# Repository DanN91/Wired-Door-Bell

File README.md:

# Wired-Door-Bell

Hear your favourite song played whenever someone rings your doorbell.

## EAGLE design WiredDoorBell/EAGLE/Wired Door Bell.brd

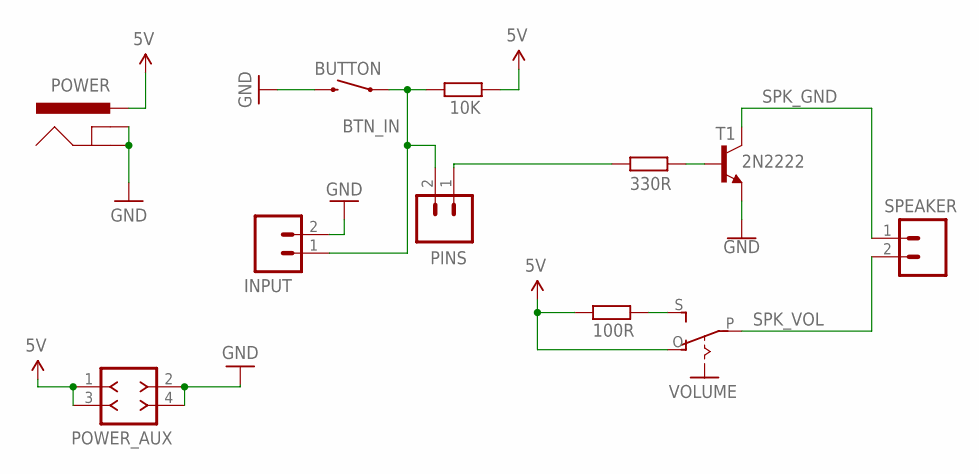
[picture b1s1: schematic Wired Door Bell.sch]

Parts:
10K: 10k; 0309V
100R: 100; 0309V
330R: 330; 0309V
BUTTON: MOMENTARY-SWITCH-SPST-PTH-6.0MM; TACTILE_SWITCH_PTH_6.0MM
INPUT: CONN_02; 1X02
PINS: CONN_02; 1X02
POWER: POWER_JACK; POWER_JACK_PTH
POWER_AUX: F-2X02-DIL-100; DIL-100-2X02
SPEAKER: CONN_02; 1X02
T1: 2N2222; TO92-EBC-OVAL
VOLUME: EG1218S; EG1218

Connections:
5V: 10K.2, 100R.1, POWER.PWR, POWER_AUX.1, POWER_AUX.3, VOLUME.O
BTN_IN: 10K.1, BUTTON.1, INPUT.1, PINS.2
GND: BUTTON.3 (2), INPUT.2, POWER.GND, POWER.GNDBREAK, POWER_AUX.2, POWER_AUX.4, T1.E
MIN: 100R.2, VOLUME.S
SPK_GND: SPEAKER.1, T1.C
SPK_PWM: 330R.1, PINS.1
SPK_SIG: 330R.2, T1.B
SPK_VOL: SPEAKER.2, VOLUME.P

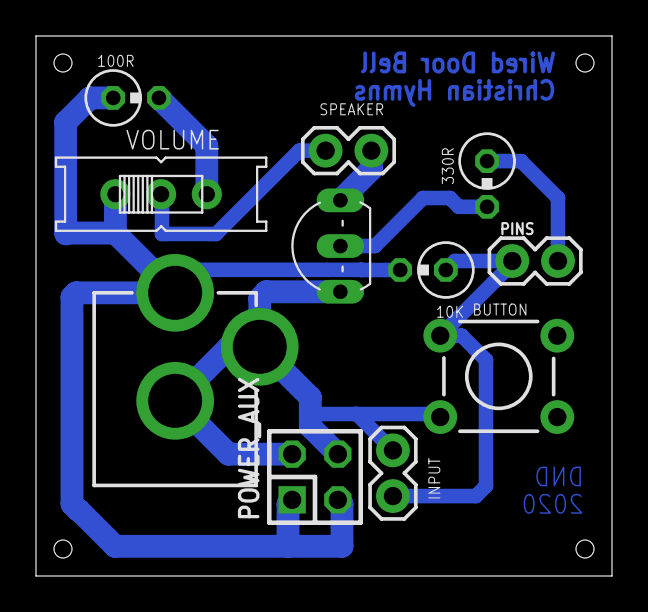
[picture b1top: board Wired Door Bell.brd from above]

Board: 2 copper layers, 32.0 x 30.0 mm, 11 parts (0 on the bottom side), 8 nets.

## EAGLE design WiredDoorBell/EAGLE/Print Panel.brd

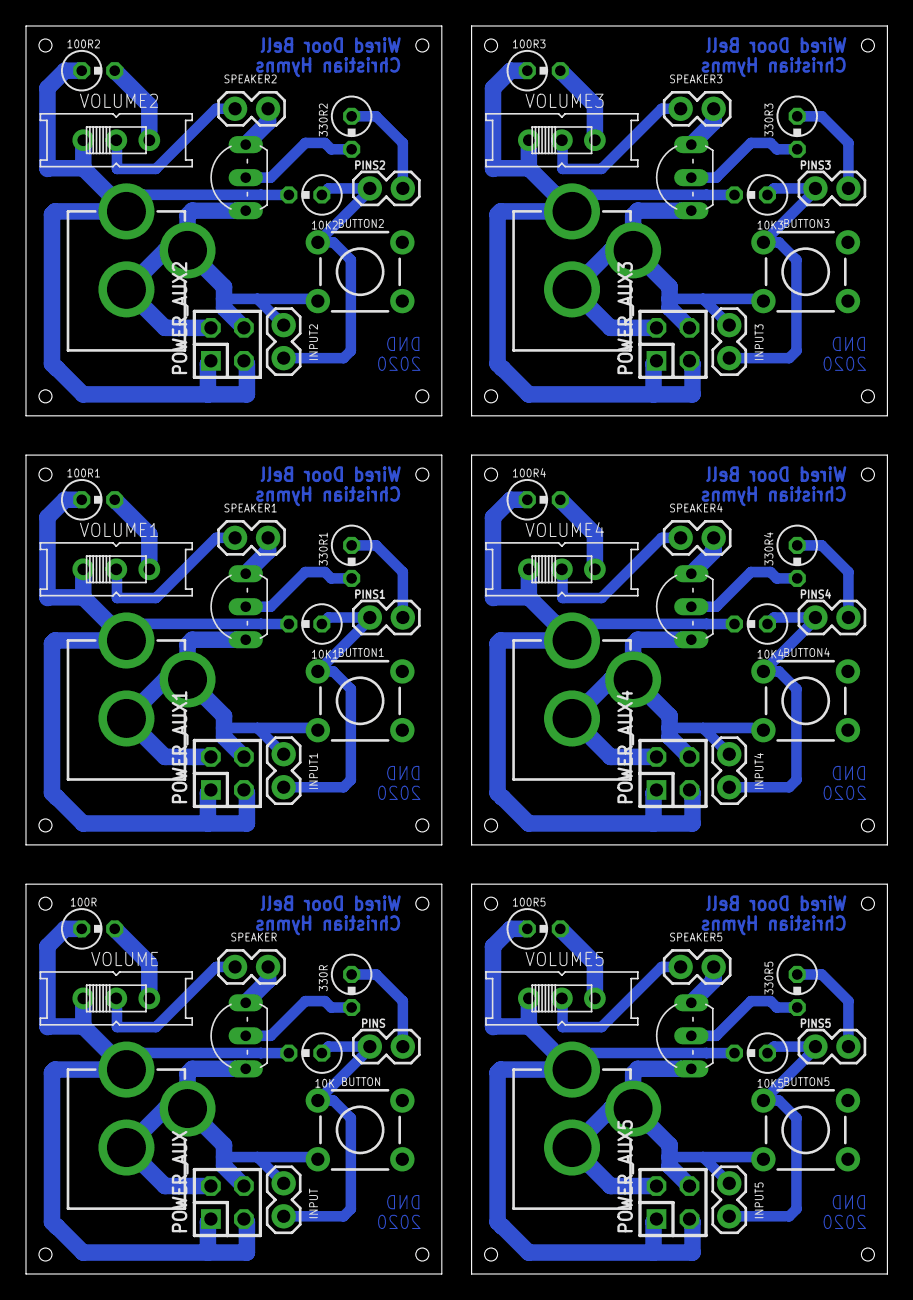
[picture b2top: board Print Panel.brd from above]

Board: 2 copper layers, 66.3 x 96.0 mm, 66 parts (0 on the bottom side), 48 nets.

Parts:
10K, 10K1, 10K2, 10K3, 10K4, 10K5: 10k; 0309V
100R, 100R1, 100R2, 100R3, 100R4, 100R5: 100; 0309V
330R, 330R1, 330R2, 330R3, 330R4, 330R5: 330; 0309V
BUTTON, BUTTON1, BUTTON2, BUTTON3, BUTTON4, BUTTON5: TACTILE_SWITCH_PTH_6.0MM
INPUT, INPUT1, INPUT2, INPUT3, INPUT4, INPUT5: 1X02
PINS, PINS1, PINS2, PINS3, PINS4, PINS5: 1X02
POWER, POWER1, POWER2, POWER3, POWER4, POWER5: POWER_JACK; POWER_JACK_PTH
POWER_AUX, POWER_AUX1, POWER_AUX2, POWER_AUX3, POWER_AUX4, POWER_AUX5: F-2X02-DIL-100; DIL-100-2X02
SPEAKER, SPEAKER1, SPEAKER2, SPEAKER3, SPEAKER4, SPEAKER5: 1X02
T1, T2, T3, T4, T5, T6: 2N2222; TO92-EBC-OVAL
VOLUME, VOLUME1, VOLUME2, VOLUME3, VOLUME4, VOLUME5: EG1218

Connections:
5V: 10K.2, 100R.1, POWER.PWR, POWER_AUX.1, POWER_AUX.3, VOLUME.O
5V1: 10K1.2, 100R1.1, POWER1.PWR, POWER_AUX1.1, POWER_AUX1.3, VOLUME1.O
5V2: 10K2.2, 100R2.1, POWER2.PWR, POWER_AUX2.1, POWER_AUX2.3, VOLUME2.O
5V3: 10K3.2, 100R3.1, POWER3.PWR, POWER_AUX3.1, POWER_AUX3.3, VOLUME3.O
5V4: 10K4.2, 100R4.1, POWER4.PWR, POWER_AUX4.1, POWER_AUX4.3, VOLUME4.O
5V5: 10K5.2, 100R5.1, POWER5.PWR, POWER_AUX5.1, POWER_AUX5.3, VOLUME5.O
BTN_IN: 10K.1, BUTTON.1, INPUT.1, PINS.2
BTN_IN1: 10K1.1, BUTTON1.1, INPUT1.1, PINS1.2
BTN_IN2: 10K2.1, BUTTON2.1, INPUT2.1, PINS2.2
BTN_IN3: 10K3.1, BUTTON3.1, INPUT3.1, PINS3.2
BTN_IN4: 10K4.1, BUTTON4.1, INPUT4.1, PINS4.2
BTN_IN5: 10K5.1, BUTTON5.1, INPUT5.1, PINS5.2
GND: BUTTON.3, INPUT.2, POWER.GND, POWER.GNDBREAK, POWER_AUX.2, POWER_AUX.4, T1.E
GND1: BUTTON1.3, INPUT1.2, POWER1.GND, POWER1.GNDBREAK, POWER_AUX1.2, POWER_AUX1.4, T2.E
GND2: BUTTON2.3, INPUT2.2, POWER2.GND, POWER2.GNDBREAK, POWER_AUX2.2, POWER_AUX2.4, T3.E
GND3: BUTTON3.3, INPUT3.2, POWER3.GND, POWER3.GNDBREAK, POWER_AUX3.2, POWER_AUX3.4, T4.E
GND4: BUTTON4.3, INPUT4.2, POWER4.GND, POWER4.GNDBREAK, POWER_AUX4.2, POWER_AUX4.4, T5.E
GND5: BUTTON5.3, INPUT5.2, POWER5.GND, POWER5.GNDBREAK, POWER_AUX5.2, POWER_AUX5.4, T6.E
MIN: 100R.2, VOLUME.S
MIN1: 100R1.2, VOLUME1.S
MIN2: 100R2.2, VOLUME2.S
MIN3: 100R3.2, VOLUME3.S
MIN4: 100R4.2, VOLUME4.S
MIN5: 100R5.2, VOLUME5.S
SPK_GND: SPEAKER.1, T1.C
SPK_GND1: SPEAKER1.1, T2.C
SPK_GND2: SPEAKER2.1, T3.C
SPK_GND3: SPEAKER3.1, T4.C
SPK_GND4: SPEAKER4.1, T5.C
SPK_GND5: SPEAKER5.1, T6.C
SPK_PWM: 330R.1, PINS.1
SPK_PWM1: 330R1.1, PINS1.1
SPK_PWM2: 330R2.1, PINS2.1
SPK_PWM3: 330R3.1, PINS3.1
SPK_PWM4: 330R4.1, PINS4.1
SPK_PWM5: 330R5.1, PINS5.1
SPK_SIG: 330R.2, T1.B
SPK_SIG1: 330R1.2, T2.B
SPK_SIG2: 330R2.2, T3.B
SPK_SIG3: 330R3.2, T4.B
SPK_SIG4: 330R4.2, T5.B
SPK_SIG5: 330R5.2, T6.B
SPK_VOL: SPEAKER.2, VOLUME.P
SPK_VOL1: SPEAKER1.2, VOLUME1.P
SPK_VOL2: SPEAKER2.2, VOLUME2.P
SPK_VOL3: SPEAKER3.2, VOLUME3.P
SPK_VOL4: SPEAKER4.2, VOLUME4.P
SPK_VOL5: SPEAKER5.2, VOLUME5.P

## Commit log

2019-11-30 BuzzerPlayer : Plays a Song via Buzzer
2020-09-16 WiredDoorBell : Press a button and enjoy the Christian song
2020-09-16 EAGLE : Added Schematic and Parts List
2020-09-28 Eagle : Added Schematic, Board and BOM
2020-09-28 PCB : Added Top and Bottom layers PDF for etching and printing
2020-10-05 Eagle : Fixed Schematics, Board and PCB
2020-10-05 main : changed pins to use Digispark ATtiny85 USB Board
2020-10-06 Eagle : Fix bottom layer for printing

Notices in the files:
parts and their libraries:
SparkFun-Switches: Licensing: Creative Commons ShareAlike 4.0 International - https://creativecommons.org/licenses/by-sa/4.0
con-headers-jp: Copyright (C) 2008, Bob Starr
